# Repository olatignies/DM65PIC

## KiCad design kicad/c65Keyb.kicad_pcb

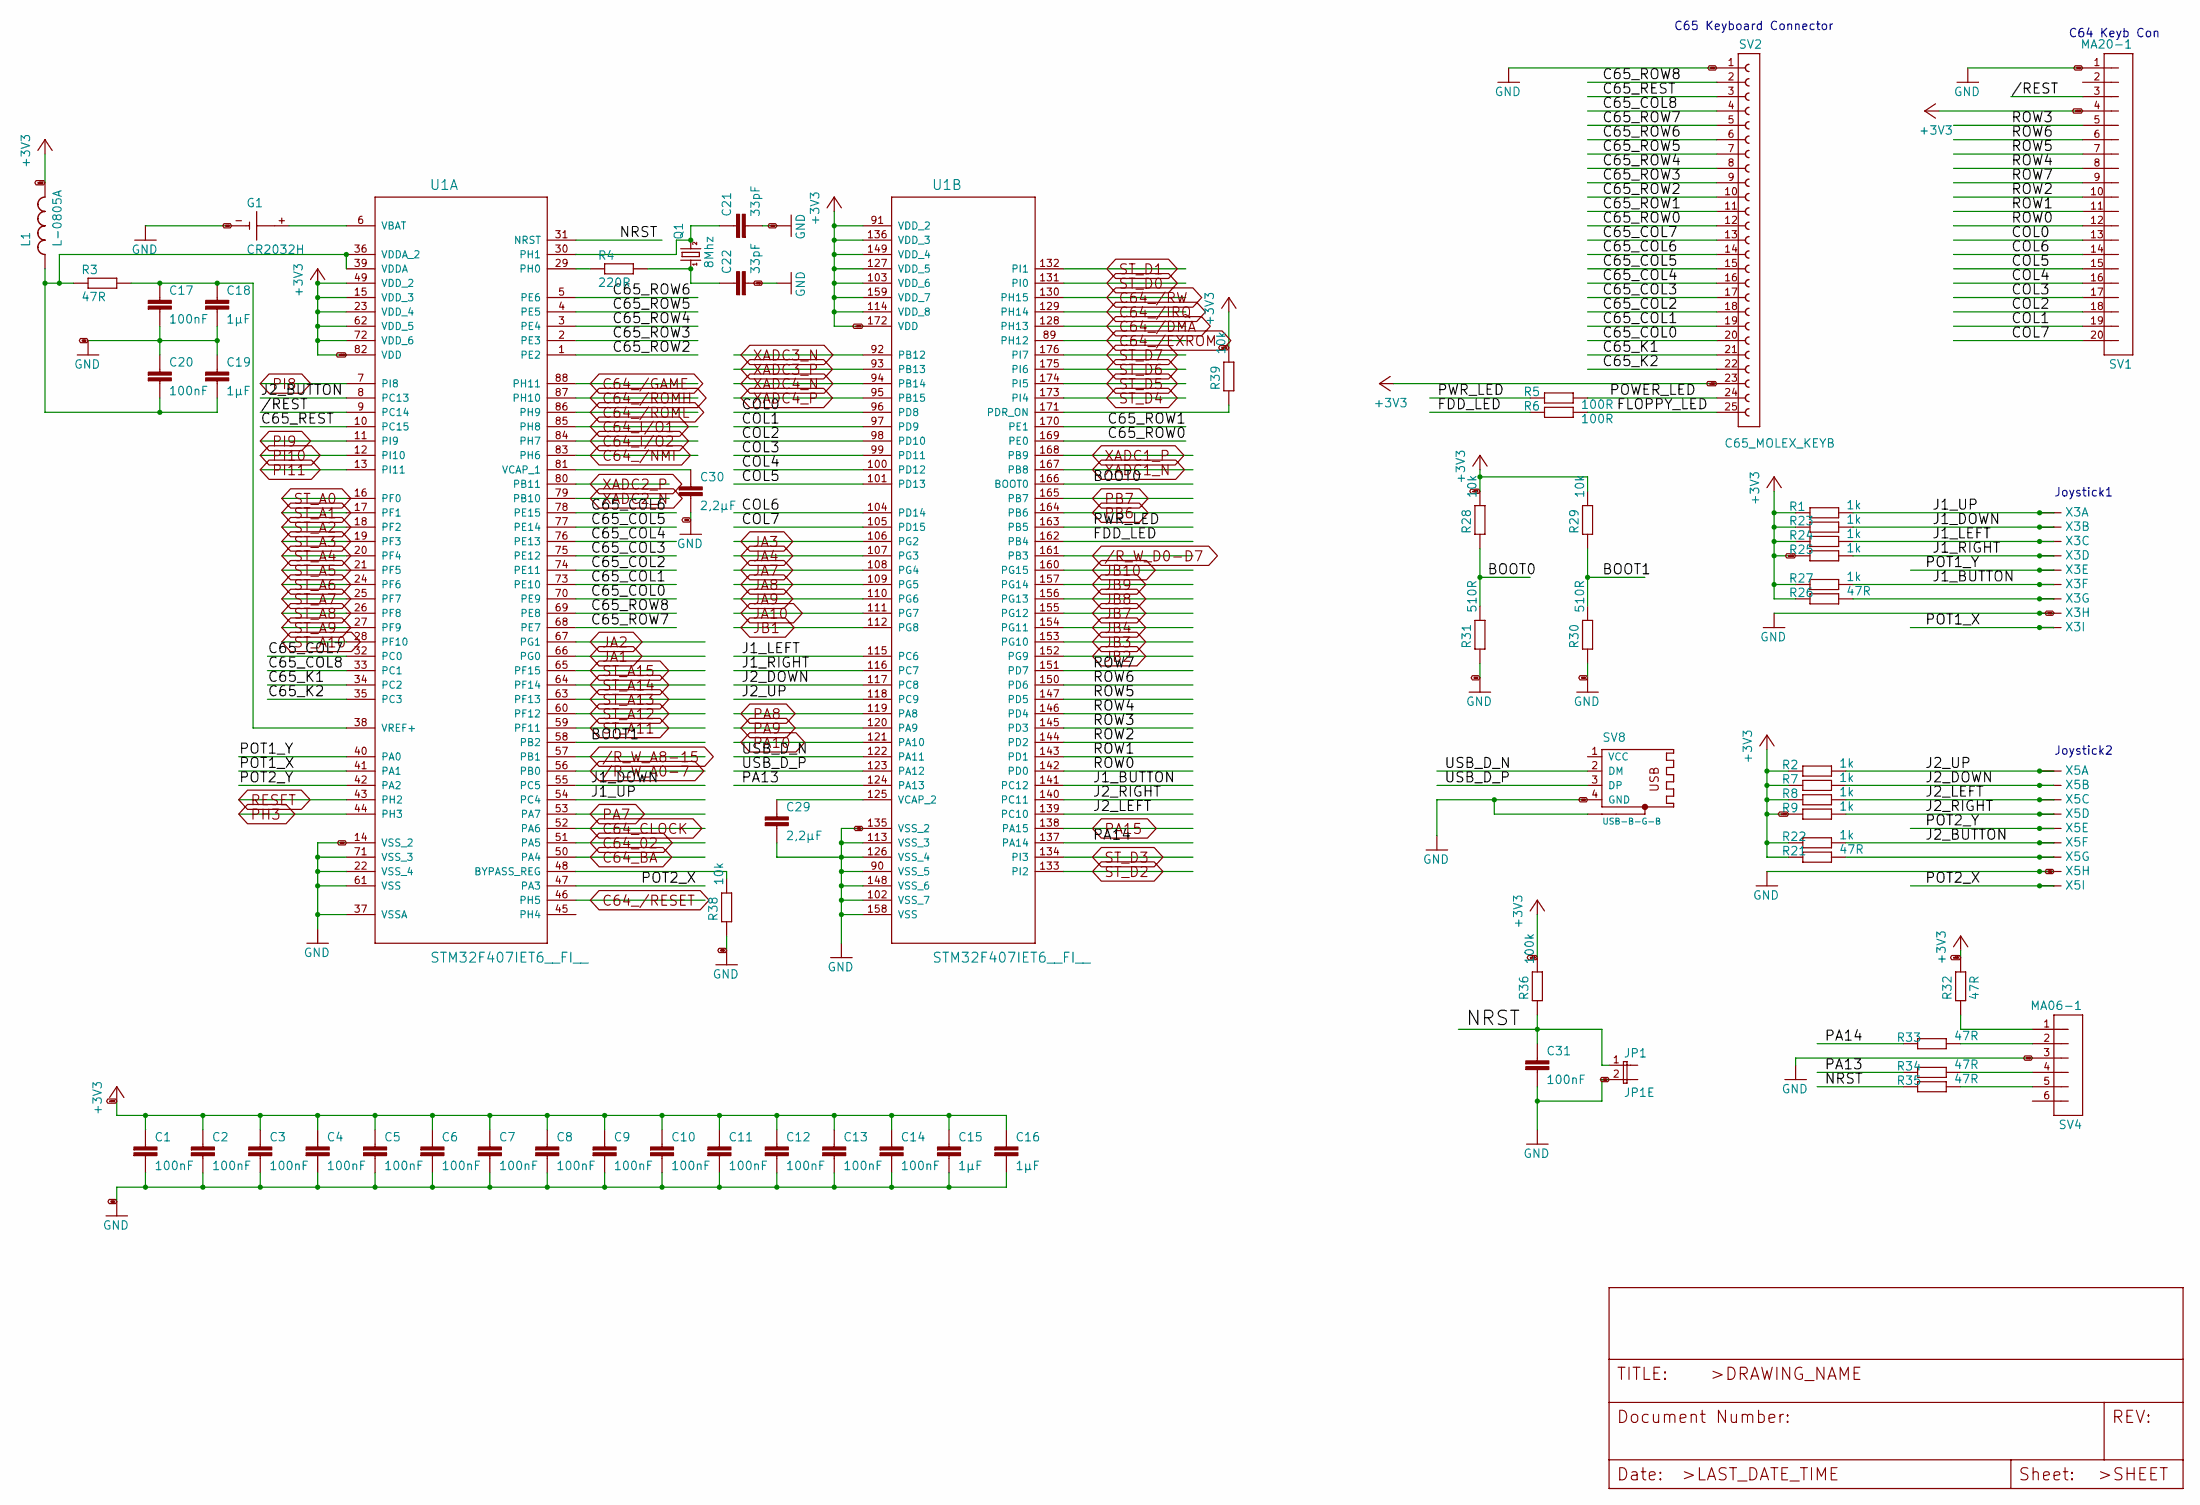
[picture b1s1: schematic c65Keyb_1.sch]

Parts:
C1, C2, C3, C4, C5, C6, C7, C8, C9, C10, C11, C12, C13, C14, C17, C20, C31: 100nF; C0805
C15, C16, C18, C19: 1µF; C0805
C21, C22: 33pF; C0805
C29, C30: 2,2µF; C0805
G1: CR2032H
JP1: JP1E; JP1
L1: L-0805A; SMD0805-ALT
Q1: 8Mhz; HC49UP
R1, R2, R7, R8, R9, R22, R23, R24, R25, R27: 1k; R0805
R3, R21, R26, R32, R33, R34, R35: 47R; R0805
R4: 220R; R0805
R5, R6: 100R; R0805
R28, R29, R38, R39: 10k; R0805
R30, R31: 510R; R0805
R36: 100k; R0805
SV1: MA20-1
SV2: C65_MOLEX_KEYB
SV4: MA06-1
SV8: USB-B-G-B; USB-B-THG-01
U1: STM32F407IET6__FI__; QFP176
X3, X5: M09?S-182; 182-009-MALE

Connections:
+3V3: C1.1, C2.1, C3.1, C4.1, C5.1, C6.1, C7.1, C8.1, C9.1, C10.1, C11.1, C12.1, C13.1, C14.1, C15.1, C16.1, L1.2, R1.1, R2.1, R7.1, R8.1, R9.1, R21.1, R22.1, R23.1, R24.1, R25.1, R26.1, R27.1, R28.2, R29.2, R32.2, R36.2, R39.2, SV1.4, SV2.23, U1.15 (VDD_3), U1.23 (VDD_4), U1.49 (VDD_2), U1.62 (VDD_5), U1.72 (VDD_6), U1.82 (VDD), U1.91 (VDD_2), U1.103 (VDD_6), U1.114 (VDD_8), U1.127 (VDD_5), U1.136 (VDD_3), U1.149 (VDD_4), U1.159 (VDD_7), U1.172 (VDD); also elsewhere on the board
/R_W_A0-7: U1.56 (PB0); also elsewhere on the board
/R_W_A8-15: U1.57 (PB1); also elsewhere on the board
/R_W_D0-D7: U1.161 (PB3); also elsewhere on the board
/c65Keyb_1//REST: SV1.3, U1.9 (PC14)
/c65Keyb_1/BOOT0: R28.1, R31.2, U1.166 (BOOT0)
/c65Keyb_1/BOOT1: R29.1, R30.2, U1.58 (PB2)
/c65Keyb_1/C65_COL0: SV2.20, U1.70 (PE9)
/c65Keyb_1/C65_COL1: SV2.19, U1.73 (PE10)
/c65Keyb_1/C65_COL2: SV2.18, U1.74 (PE11)
/c65Keyb_1/C65_COL3: SV2.17, U1.75 (PE12)
/c65Keyb_1/C65_COL4: SV2.16, U1.76 (PE13)
/c65Keyb_1/C65_COL5: SV2.15, U1.77 (PE14)
/c65Keyb_1/C65_COL6: SV2.14, U1.78 (PE15)
/c65Keyb_1/C65_COL7: SV2.13, U1.32 (PC0)
/c65Keyb_1/C65_COL8: SV2.4, U1.33 (PC1)
/c65Keyb_1/C65_K1: SV2.21, U1.34 (PC2)
/c65Keyb_1/C65_K2: SV2.22, U1.35 (PC3)
/c65Keyb_1/C65_REST: SV2.3, U1.10 (PC15)
/c65Keyb_1/C65_ROW0: SV2.12, U1.169 (PE0)
/c65Keyb_1/C65_ROW1: SV2.11, U1.170 (PE1)
/c65Keyb_1/C65_ROW2: SV2.10, U1.1 (PE2)
/c65Keyb_1/C65_ROW3: SV2.9, U1.2 (PE3)
/c65Keyb_1/C65_ROW4: SV2.8, U1.3 (PE4)
/c65Keyb_1/C65_ROW5: SV2.7, U1.4 (PE5)
/c65Keyb_1/C65_ROW6: SV2.6, U1.5 (PE6)
/c65Keyb_1/C65_ROW7: SV2.5, U1.68 (PE7)
/c65Keyb_1/C65_ROW8: SV2.2, U1.69 (PE8)
/c65Keyb_1/COL0: SV1.13, U1.96 (PD8)
/c65Keyb_1/COL1: SV1.19, U1.97 (PD9)
/c65Keyb_1/COL2: SV1.18, U1.98 (PD10)
/c65Keyb_1/COL3: SV1.17, U1.99 (PD11)
/c65Keyb_1/COL4: SV1.16, U1.100 (PD12)
/c65Keyb_1/COL5: SV1.15, U1.101 (PD13)
/c65Keyb_1/COL6: SV1.14, U1.104 (PD14)
/c65Keyb_1/COL7: SV1.20, U1.105 (PD15)
/c65Keyb_1/FDD_LED: R6.1, U1.162 (PB4)
/c65Keyb_1/FLOPPY_LED: R6.2, SV2.25
/c65Keyb_1/J1_BUTTON: R27.2, U1.141 (PC12), X3.6
/c65Keyb_1/J1_DOWN: R23.2, U1.55 (PC5), X3.2
/c65Keyb_1/J1_LEFT: R24.2, U1.115 (PC6), X3.3
/c65Keyb_1/J1_RIGHT: R25.2, U1.116 (PC7), X3.4
/c65Keyb_1/J1_UP: R1.2, U1.54 (PC4), X3.1
/c65Keyb_1/J2_BUTTON: R22.2, U1.8 (PC13), X5.6
/c65Keyb_1/J2_DOWN: R7.2, U1.117 (PC8), X5.2
/c65Keyb_1/J2_LEFT: R8.2, U1.139 (PC10), X5.3
/c65Keyb_1/J2_RIGHT: R9.2, U1.140 (PC11), X5.4
/c65Keyb_1/J2_UP: R2.2, U1.118 (PC9), X5.1
/c65Keyb_1/NRST: C31.1, JP1.1, R35.1, R36.1, U1.31 (NRST)
/c65Keyb_1/PA13: R34.1, U1.124 (PA13)
/c65Keyb_1/PA14: R33.1, U1.137 (PA14)
/c65Keyb_1/POT1_X: U1.41 (PA1), X3.9
/c65Keyb_1/POT1_Y: U1.40 (PA0), X3.5
/c65Keyb_1/POT2_X: U1.47 (PA3), X5.9
/c65Keyb_1/POT2_Y: U1.42 (PA2), X5.5
/c65Keyb_1/POWER_LED: R5.2, SV2.24
/c65Keyb_1/PWR_LED: R5.1, U1.163 (PB5)
/c65Keyb_1/ROW0: SV1.12, U1.142 (PD0)
/c65Keyb_1/ROW1: SV1.11, U1.143 (PD1)
/c65Keyb_1/ROW2: SV1.10, U1.144 (PD2)
/c65Keyb_1/ROW3: SV1.5, U1.145 (PD3)
/c65Keyb_1/ROW4: SV1.8, U1.146 (PD4)
/c65Keyb_1/ROW5: SV1.7, U1.147 (PD5)
/c65Keyb_1/ROW6: SV1.6, U1.150 (PD6)
/c65Keyb_1/ROW7: SV1.9, U1.151 (PD7)
/c65Keyb_1/USB_D_N: SV8.2 (DM), U1.122 (PA11)
/c65Keyb_1/USB_D_P: SV8.3 (DP), U1.123 (PA12)
C64_02: U1.51 (PA5); also elsewhere on the board
C64_/DMA: U1.128 (PH13); also elsewhere on the board
C64_/EXROM: U1.89 (PH12); also elsewhere on the board
C64_/GAME: U1.88 (PH11); also elsewhere on the board
C64_/IRQ: U1.129 (PH14); also elsewhere on the board
C64_/NMI: U1.83 (PH6); also elsewhere on the board
C64_/RESET: U1.46 (PH5); also elsewhere on the board
C64_/ROMH: U1.87 (PH10); also elsewhere on the board
C64_/ROML: U1.86 (PH9); also elsewhere on the board
C64_/RW: U1.130 (PH15); also elsewhere on the board
C64_BA: U1.50 (PA4); also elsewhere on the board
C64_CLOCK: U1.52 (PA6); also elsewhere on the board
C64_I/O1: U1.85 (PH8); also elsewhere on the board
C64_I/O2: U1.84 (PH7); also elsewhere on the board
GND: C1.2, C2.2, C3.2, C4.2, C5.2, C6.2, C7.2, C8.2, C9.2, C10.2, C11.2, C12.2, C13.2, C14.2, C15.2, C16.2, C17.2, C18.2, C19.1, C20.1, C21.2, C22.2, C29.2, C30.2, C31.2, G1.-, JP1.2, R30.1, R31.1, R38.1, SV1.1, SV2.1, SV4.3, SV8.4 (GND), SV8.G1, U1.14 (VSS_2), U1.22 (VSS_4), U1.37 (VSSA), U1.61 (VSS), U1.71 (VSS_3), U1.90 (VSS_5), U1.102 (VSS_7), U1.113 (VSS_3), U1.126 (VSS_4), U1.135 (VSS_2), U1.148 (VSS_6), U1.158 (VSS), X3.8, X5.8; also elsewhere on the board
JA1: U1.66 (PG0); also elsewhere on the board
JA2: U1.67 (PG1); also elsewhere on the board
JA3: U1.106 (PG2); also elsewhere on the board
JA4: U1.107 (PG3); also elsewhere on the board
JA7: U1.108 (PG4); also elsewhere on the board
JA8: U1.109 (PG5); also elsewhere on the board
JA9: U1.110 (PG6); also elsewhere on the board
JA10: U1.111 (PG7); also elsewhere on the board
JB1: U1.112 (PG8); also elsewhere on the board
JB2: U1.152 (PG9); also elsewhere on the board
JB3: U1.153 (PG10); also elsewhere on the board
JB4: U1.154 (PG11); also elsewhere on the board
JB7: U1.155 (PG12); also elsewhere on the board
JB8: U1.156 (PG13); also elsewhere on the board
JB9: U1.157 (PG14); also elsewhere on the board
JB10: U1.160 (PG15); also elsewhere on the board
unnamed: C17.1, C18.1, R3.2, U1.38 (VREF+)
unnamed: C19.2, C20.2, L1.1, R3.1, U1.36 (VDDA_2), U1.39 (VDDA)
unnamed: C21.1, Q1.2, U1.30 (PH1)
unnamed: C22.1, Q1.1, R4.2
unnamed: C29.1, U1.125 (VCAP_2)
unnamed: C30.1, U1.81 (VCAP_1)
unnamed: G1.+, U1.6 (VBAT)
unnamed: R4.1, U1.29 (PH0)
unnamed: R21.2, X5.7
unnamed: R26.2, X3.7
unnamed: R32.1, SV4.1
unnamed: R33.2, SV4.2
unnamed: R34.2, SV4.4
unnamed: R35.2, SV4.5
unnamed: R38.2, U1.48 (BYPASS_REG)
unnamed: R39.1, U1.171 (PDR_ON)
PA7: U1.53 (PA7); also elsewhere on the board
PA8: U1.119 (PA8); also elsewhere on the board
PA9: U1.120 (PA9); also elsewhere on the board
PA10: U1.121 (PA10); also elsewhere on the board
PA15: U1.138 (PA15); also elsewhere on the board
PB6: U1.164 (PB6); also elsewhere on the board
PB7: U1.165 (PB7); also elsewhere on the board
PH3: U1.44 (PH3); also elsewhere on the board
PI8: U1.7 (PI8); also elsewhere on the board
PI9: U1.11 (PI9); also elsewhere on the board
PI10: U1.12 (PI10); also elsewhere on the board
PI11: U1.13 (PI11); also elsewhere on the board
RESET: U1.43 (PH2); also elsewhere on the board
ST_A0: U1.16 (PF0); also elsewhere on the board
ST_A1: U1.17 (PF1); also elsewhere on the board
ST_A2: U1.18 (PF2); also elsewhere on the board
ST_A3: U1.19 (PF3); also elsewhere on the board
ST_A4: U1.20 (PF4); also elsewhere on the board
ST_A5: U1.21 (PF5); also elsewhere on the board
ST_A6: U1.24 (PF6); also elsewhere on the board
ST_A7: U1.25 (PF7); also elsewhere on the board
ST_A8: U1.26 (PF8); also elsewhere on the board
ST_A9: U1.27 (PF9); also elsewhere on the board
ST_A10: U1.28 (PF10); also elsewhere on the board
ST_A11: U1.59 (PF11); also elsewhere on the board
ST_A12: U1.60 (PF12); also elsewhere on the board
ST_A13: U1.63 (PF13); also elsewhere on the board
ST_A14: U1.64 (PF14); also elsewhere on the board
ST_A15: U1.65 (PF15); also elsewhere on the board
ST_D0: U1.131 (PI0); also elsewhere on the board
ST_D1: U1.132 (PI1); also elsewhere on the board
ST_D2: U1.133 (PI2); also elsewhere on the board
ST_D3: U1.134 (PI3); also elsewhere on the board
ST_D4: U1.173 (PI4); also elsewhere on the board
ST_D5: U1.174 (PI5); also elsewhere on the board
ST_D6: U1.175 (PI6); also elsewhere on the board
ST_D7: U1.176 (PI7); also elsewhere on the board
XADC1_N: U1.167 (PB8); also elsewhere on the board
XADC1_P: U1.168 (PB9); also elsewhere on the board
XADC2_N: U1.79 (PB10); also elsewhere on the board
XADC2_P: U1.80 (PB11); also elsewhere on the board
XADC3_N: U1.92 (PB12); also elsewhere on the board
XADC3_P: U1.93 (PB13); also elsewhere on the board
XADC4_N: U1.94 (PB14); also elsewhere on the board
XADC4_P: U1.95 (PB15); also elsewhere on the board

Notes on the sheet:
C64 Keyb Con
Joystick1
Joystick2
C65 Keyboard Connector

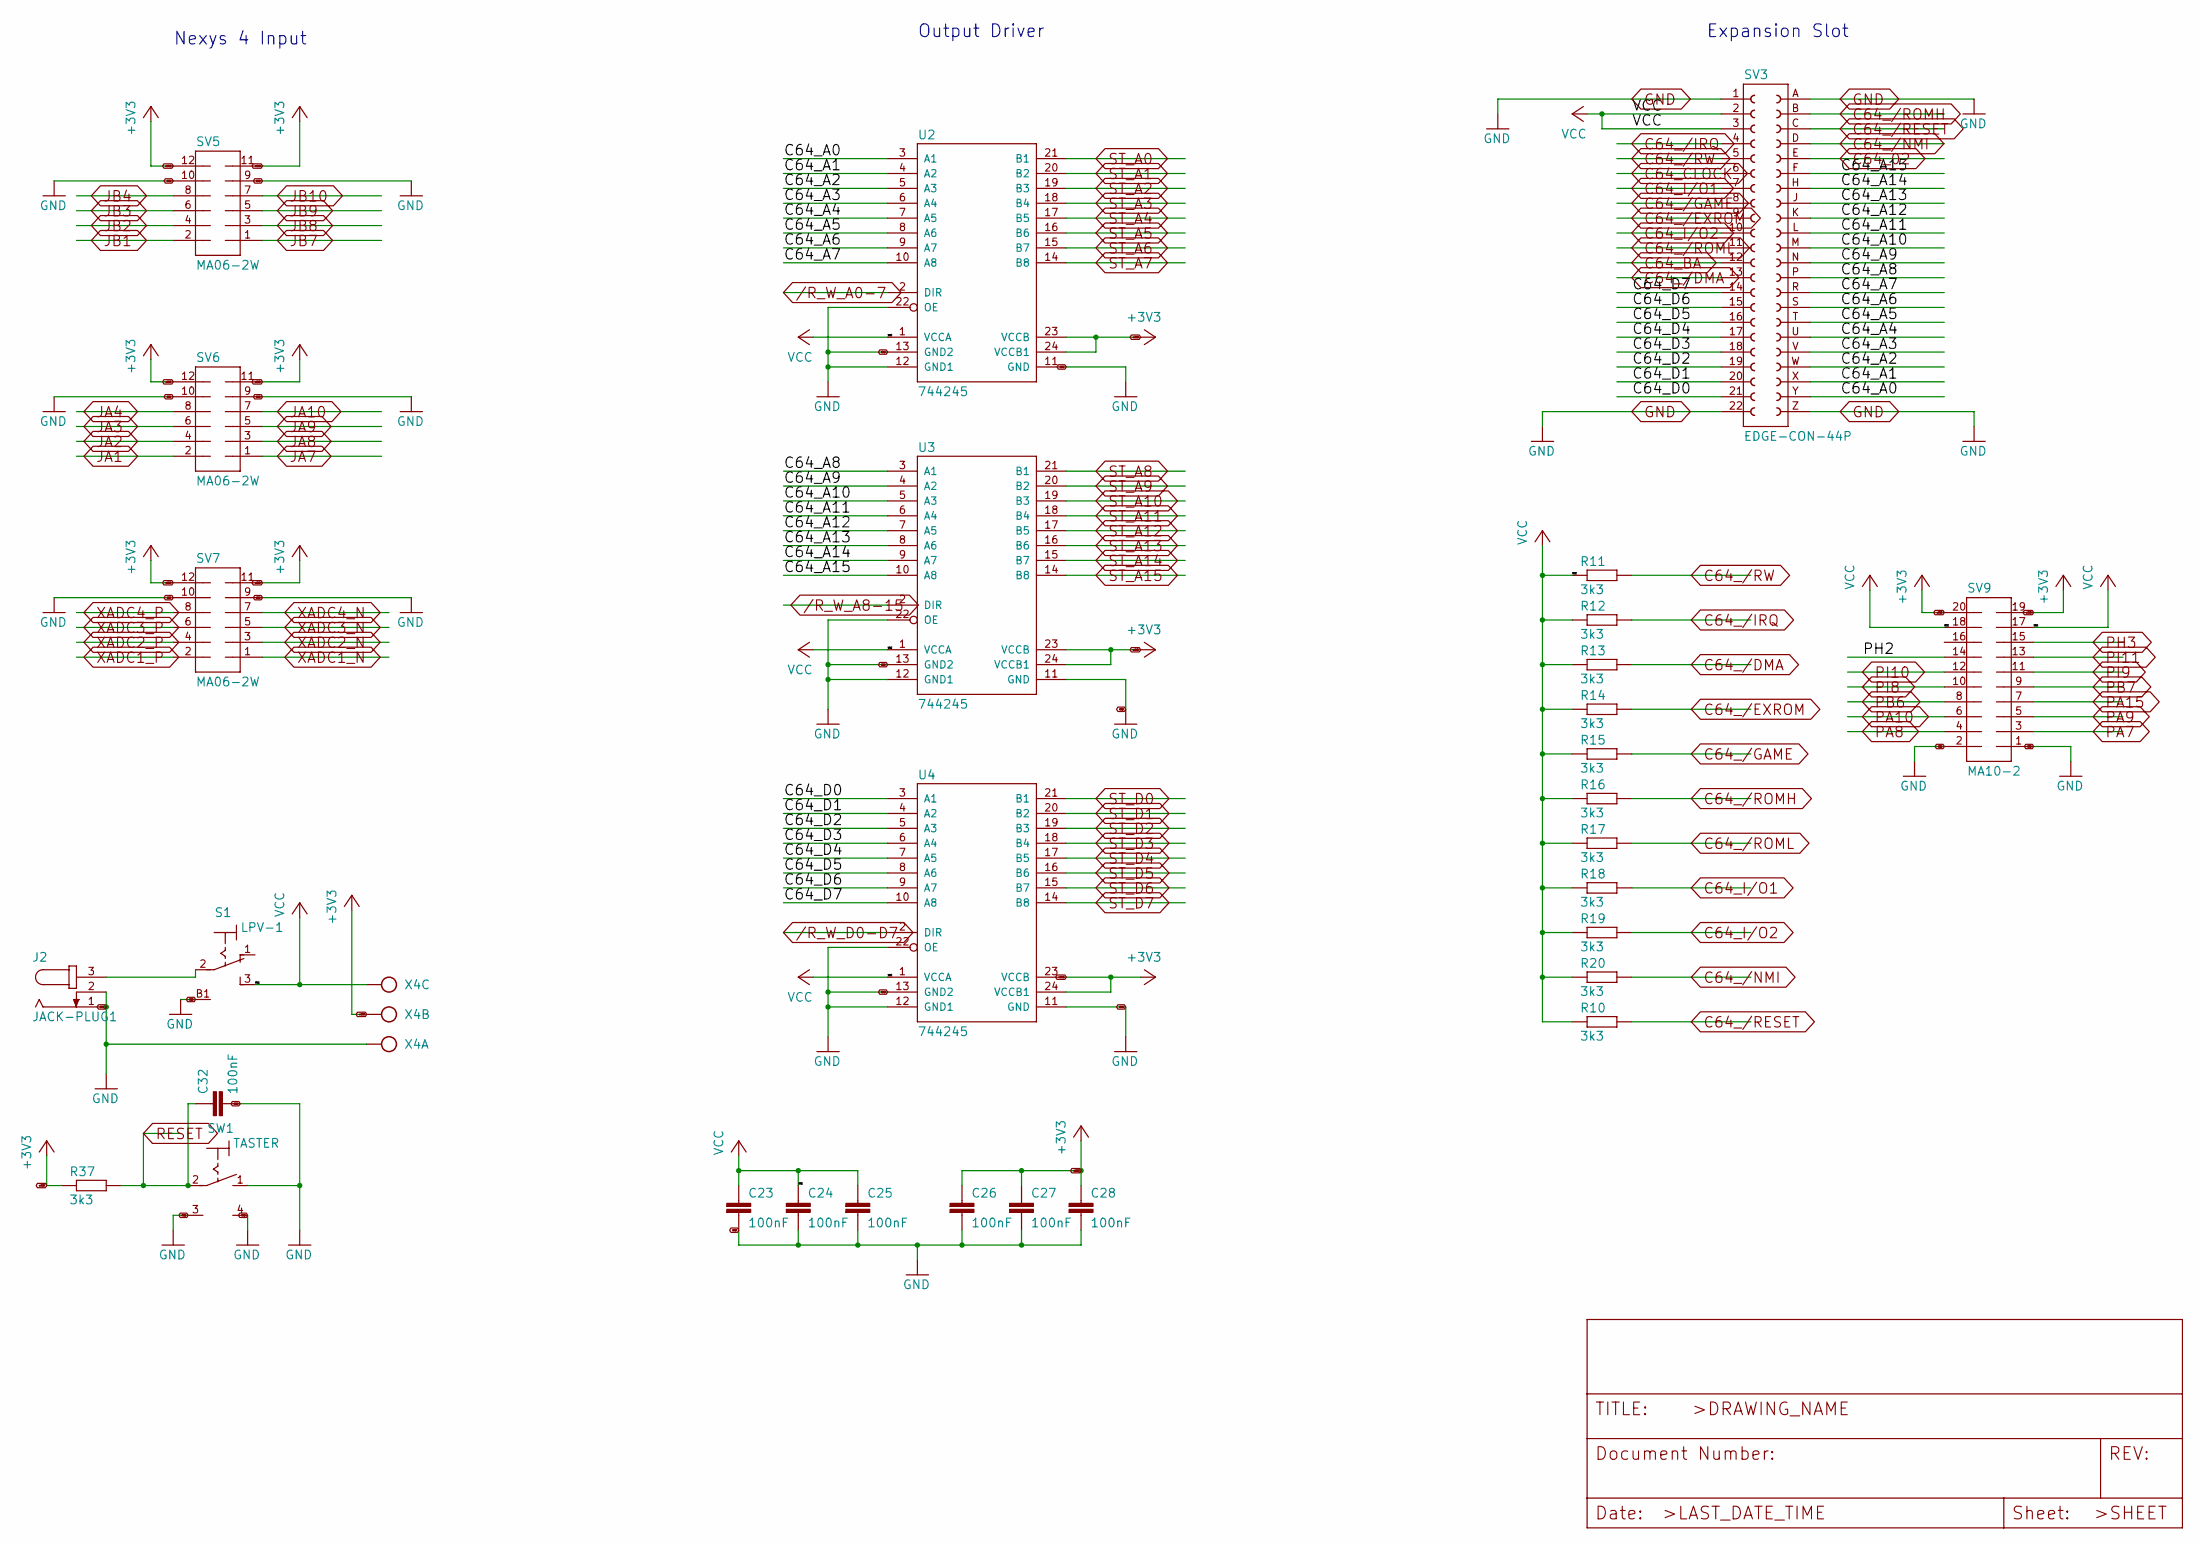
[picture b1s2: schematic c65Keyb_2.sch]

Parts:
C23, C24, C25, C26, C27, C28, C32: 100nF; C0805
J2: JACK-PLUG1; SPC4078
R10, R11, R12, R13, R14, R15, R16, R17, R18, R19, R20, R37: 3k3; R0805
S1: LPV-1
SV3: EDGE-CON-44P; EDGE-CON-44
SV5, SV6, SV7: MA06-2W
SV9: MA10-2
SW1: TASTER; MICRO_SWITCH
U2, U3, U4: 744245; SO24L
X4: MKDS_5_3-6,35; MKDS_5_3-635

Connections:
+3V3: C26.1, C27.1, C28.1, R37.1, SV5.11, SV5.12, SV6.11, SV6.12, SV7.11, SV7.12, SV9.19, SV9.20, U2.23 (VCCB), U2.24 (VCCB1), U3.23 (VCCB), U3.24 (VCCB1), U4.23 (VCCB), U4.24 (VCCB1), X4.2; also elsewhere on the board
/R_W_A0-7: U2.2 (DIR); also elsewhere on the board
/R_W_A8-15: U3.2 (DIR); also elsewhere on the board
/R_W_D0-D7: U4.2 (DIR); also elsewhere on the board
/c65Keyb_2/C64_A0: SV3.Y, U2.3 (A1)
/c65Keyb_2/C64_A1: SV3.X, U2.4 (A2)
/c65Keyb_2/C64_A2: SV3.W, U2.5 (A3)
/c65Keyb_2/C64_A3: SV3.V, U2.6 (A4)
/c65Keyb_2/C64_A4: SV3.U, U2.7 (A5)
/c65Keyb_2/C64_A5: SV3.T, U2.8 (A6)
/c65Keyb_2/C64_A6: SV3.S, U2.9 (A7)
/c65Keyb_2/C64_A7: SV3.R, U2.10 (A8)
/c65Keyb_2/C64_A8: SV3.P, U3.3 (A1)
/c65Keyb_2/C64_A9: SV3.N, U3.4 (A2)
/c65Keyb_2/C64_A10: SV3.M, U3.5 (A3)
/c65Keyb_2/C64_A11: SV3.L, U3.6 (A4)
/c65Keyb_2/C64_A12: SV3.K, U3.7 (A5)
/c65Keyb_2/C64_A13: SV3.J, U3.8 (A6)
/c65Keyb_2/C64_A14: SV3.H, U3.9 (A7)
/c65Keyb_2/C64_A15: SV3.F, U3.10 (A8)
/c65Keyb_2/C64_D0: SV3.21, U4.3 (A1)
/c65Keyb_2/C64_D1: SV3.20, U4.4 (A2)
/c65Keyb_2/C64_D2: SV3.19, U4.5 (A3)
/c65Keyb_2/C64_D3: SV3.18, U4.6 (A4)
/c65Keyb_2/C64_D4: SV3.17, U4.7 (A5)
/c65Keyb_2/C64_D5: SV3.16, U4.8 (A6)
/c65Keyb_2/C64_D6: SV3.15, U4.9 (A7)
/c65Keyb_2/C64_D7: SV3.14, U4.10 (A8)
/c65Keyb_2/PH2: SV9.14
C64_02: SV3.E; also elsewhere on the board
C64_/DMA: R13.2, SV3.13; also elsewhere on the board
C64_/EXROM: R14.2, SV3.9; also elsewhere on the board
C64_/GAME: R15.2, SV3.8; also elsewhere on the board
C64_/IRQ: R12.2, SV3.4; also elsewhere on the board
C64_/NMI: R20.2, SV3.D; also elsewhere on the board
C64_/RESET: R10.2, SV3.C; also elsewhere on the board
C64_/ROMH: R16.2, SV3.B; also elsewhere on the board
C64_/ROML: R17.2, SV3.11; also elsewhere on the board
C64_/RW: R11.2, SV3.5; also elsewhere on the board
C64_BA: SV3.12; also elsewhere on the board
C64_CLOCK: SV3.6; also elsewhere on the board
C64_I/O1: R18.2, SV3.7; also elsewhere on the board
C64_I/O2: R19.2, SV3.10; also elsewhere on the board
GND: C23.2, C24.2, C25.2, C26.2, C27.2, C28.2, C32.2, J2.1, J2.2, S1.B1 (B), SV3.1, SV3.22, SV3.A, SV3.Z, SV5.9, SV5.10, SV6.9, SV6.10, SV7.9, SV7.10, SV9.1, SV9.2, SW1.1 (O), SW1.3 (B), SW1.4 (B1), U2.11 (GND), U2.12 (GND1), U2.13 (GND2), U2.22 (OE), U3.11 (GND), U3.12 (GND1), U3.13 (GND2), U3.22 (OE), U4.11 (GND), U4.12 (GND1), U4.13 (GND2), U4.22 (OE), X4.1; also elsewhere on the board
JA1: SV6.2; also elsewhere on the board
JA2: SV6.4; also elsewhere on the board
JA3: SV6.6; also elsewhere on the board
JA4: SV6.8; also elsewhere on the board
JA7: SV6.1; also elsewhere on the board
JA8: SV6.3; also elsewhere on the board
JA9: SV6.5; also elsewhere on the board
JA10: SV6.7; also elsewhere on the board
JB1: SV5.2; also elsewhere on the board
JB2: SV5.4; also elsewhere on the board
JB3: SV5.6; also elsewhere on the board
JB4: SV5.8; also elsewhere on the board
JB7: SV5.1; also elsewhere on the board
JB8: SV5.3; also elsewhere on the board
JB9: SV5.5; also elsewhere on the board
JB10: SV5.7; also elsewhere on the board
unnamed: J2.3, S1.2
PA7: SV9.3; also elsewhere on the board
PA8: SV9.4; also elsewhere on the board
PA9: SV9.5; also elsewhere on the board
PA10: SV9.6; also elsewhere on the board
PA15: SV9.7; also elsewhere on the board
PB6: SV9.8; also elsewhere on the board
PB7: SV9.9; also elsewhere on the board
PH3: SV9.15; also elsewhere on the board
PI8: SV9.10; also elsewhere on the board
PI9: SV9.11; also elsewhere on the board
PI10: SV9.12; also elsewhere on the board
PI11: SV9.13; also elsewhere on the board
RESET: C32.1, R37.2, SW1.2; also elsewhere on the board
ST_A0: U2.21 (B1); also elsewhere on the board
ST_A1: U2.20 (B2); also elsewhere on the board
ST_A2: U2.19 (B3); also elsewhere on the board
ST_A3: U2.18 (B4); also elsewhere on the board
ST_A4: U2.17 (B5); also elsewhere on the board
ST_A5: U2.16 (B6); also elsewhere on the board
ST_A6: U2.15 (B7); also elsewhere on the board
ST_A7: U2.14 (B8); also elsewhere on the board
ST_A8: U3.21 (B1); also elsewhere on the board
ST_A9: U3.20 (B2); also elsewhere on the board
ST_A10: U3.19 (B3); also elsewhere on the board
ST_A11: U3.18 (B4); also elsewhere on the board
ST_A12: U3.17 (B5); also elsewhere on the board
ST_A13: U3.16 (B6); also elsewhere on the board
ST_A14: U3.15 (B7); also elsewhere on the board
ST_A15: U3.14 (B8); also elsewhere on the board
ST_D0: U4.21 (B1); also elsewhere on the board
ST_D1: U4.20 (B2); also elsewhere on the board
ST_D2: U4.19 (B3); also elsewhere on the board
ST_D3: U4.18 (B4); also elsewhere on the board
ST_D4: U4.17 (B5); also elsewhere on the board
ST_D5: U4.16 (B6); also elsewhere on the board
ST_D6: U4.15 (B7); also elsewhere on the board
ST_D7: U4.14 (B8); also elsewhere on the board
VCC: C23.1, C24.1, C25.1, R10.1, R11.1, R12.1, R13.1, R14.1, R15.1, R16.1, R17.1, R18.1, R19.1, R20.1, S1.3 (S), SV3.2, SV3.3, SV9.17, SV9.18, U2.1 (VCCA), U3.1 (VCCA), U4.1 (VCCA), X4.3
XADC1_N: SV7.1; also elsewhere on the board
XADC1_P: SV7.2; also elsewhere on the board
XADC2_N: SV7.3; also elsewhere on the board
XADC2_P: SV7.4; also elsewhere on the board
XADC3_N: SV7.5; also elsewhere on the board
XADC3_P: SV7.6; also elsewhere on the board
XADC4_N: SV7.7; also elsewhere on the board
XADC4_P: SV7.8; also elsewhere on the board

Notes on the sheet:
Expansion Slot
Output Driver
Nexys 4 Input

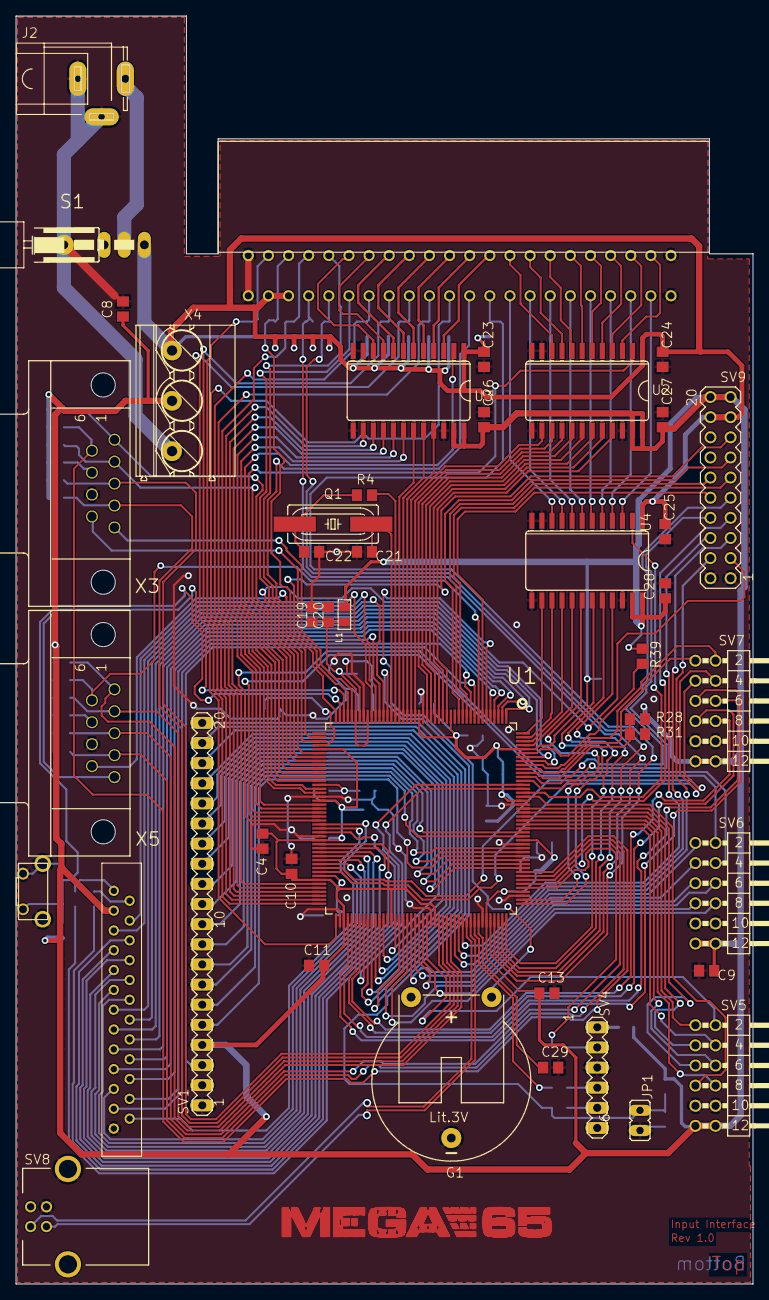
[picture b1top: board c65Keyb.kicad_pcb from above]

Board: 2 copper layers, 93.0 x 160.0 mm, 94 parts (0 on the bottom side), 185 nets.

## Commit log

2021-07-03 kicad conversion. Still needs to be cleaned up
2021-07-11 Refill, check DRC
